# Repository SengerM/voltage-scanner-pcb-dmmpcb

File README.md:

# voltage-scanner-pcb-dmmpcb

[KiCad](http://kicad-pcb.org/) project for the DMMPCB board. This board implements the handling of the voltmeter. The schematic of this board can be found in [this link](export/DMMPCB.pdf). Below is the layout.

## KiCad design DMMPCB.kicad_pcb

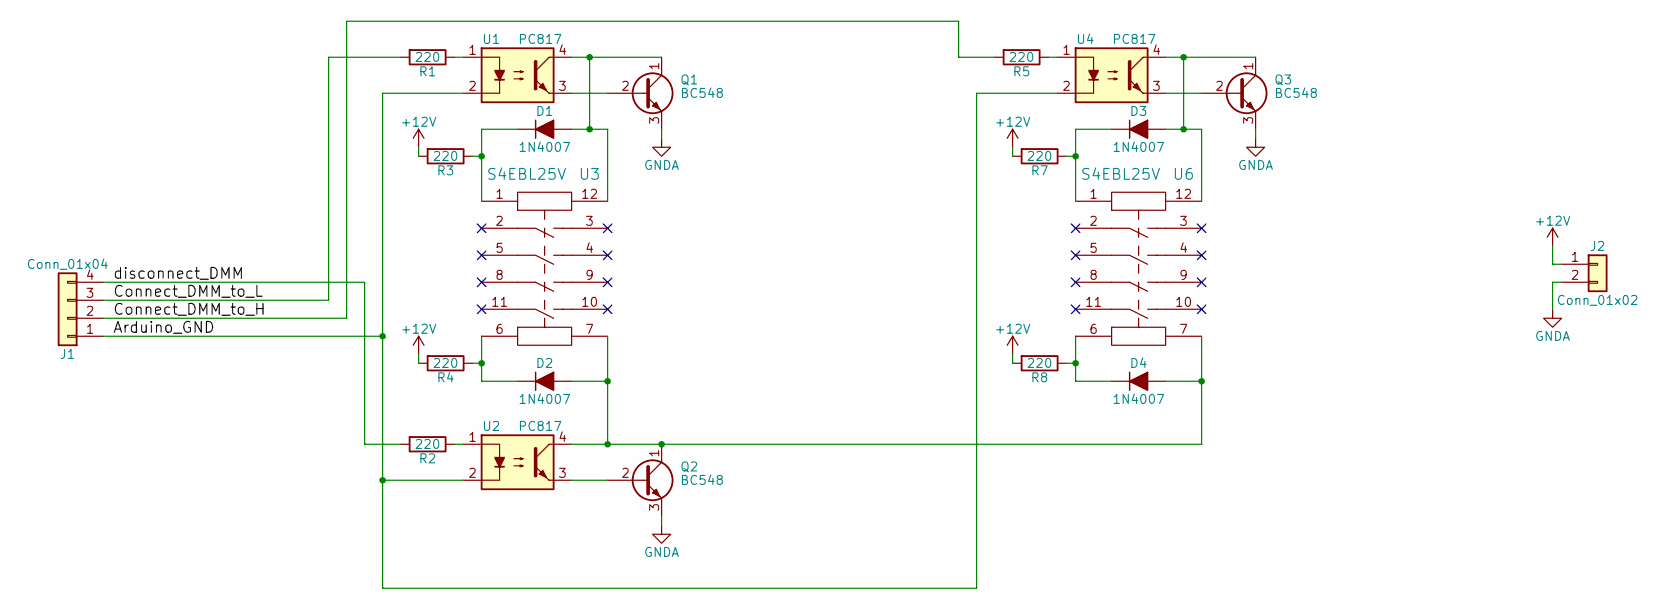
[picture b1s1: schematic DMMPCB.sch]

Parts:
D1, D2, D3, D4: 1N4007; D_SMA-SMB_Universal_Handsoldering
J1: Conn_01x04; Pin_Header_Straight_1x04_Pitch2.54mm
J2: Conn_01x02; Pin_Header_Straight_2x01_Pitch2.54mm
Q1, Q2, Q3: BC548; TO-92_Molded_Narrow_CUSTOM_PADS
R1, R2, R3, R4, R5, R7, R8: 220; R_1206_HandSoldering
U1, U2, U4: PC817; DIP-4_W7.62mm
U3, U6: S4EBL25V

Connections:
+12V: J2.1, R3.2, R4.2, R7.2, R8.2
/Arduino_GND: J1.1, U1.2, U2.2, U4.2
/Connect_DMM_to_H: J1.2, R5.2
/Connect_DMM_to_L: J1.3, R1.2
/disconnect_DMM: J1.4, R2.2
GNDA: J2.2, Q1.3 (E), Q2.3 (E), Q3.3 (E)
unnamed: D1.1 (K), R3.1, U3.1
unnamed: D1.2 (A), Q1.1 (C), U1.4, U3.12
unnamed: D2.1 (K), R4.1, U3.6
unnamed: D2.2 (A), D4.2 (A), Q2.1 (C), U2.4, U3.7, U6.7
unnamed: D3.1 (K), R7.1, U6.1
unnamed: D3.2 (A), Q3.1 (C), U4.4, U6.12
unnamed: D4.1 (K), R8.1, U6.6
unnamed: Q1.2 (B), U1.3
unnamed: Q2.2 (B), U2.3
unnamed: Q3.2 (B), U4.3
unnamed: R1.1, U1.1
unnamed: R2.1, U2.1
unnamed: R5.1, U4.1

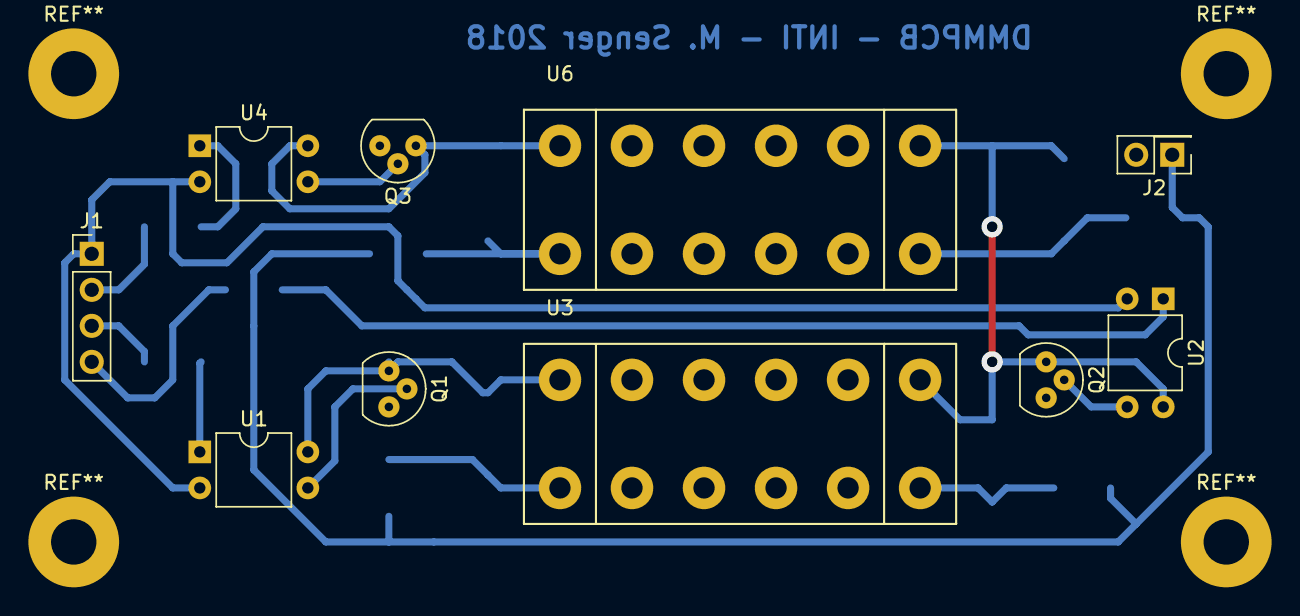
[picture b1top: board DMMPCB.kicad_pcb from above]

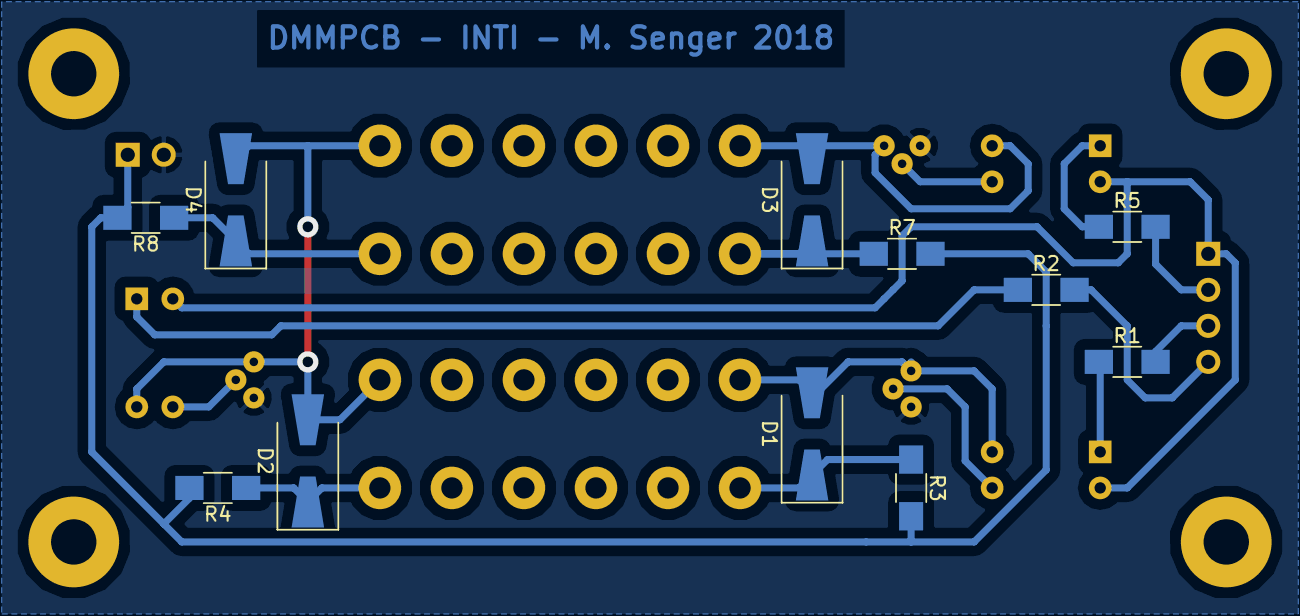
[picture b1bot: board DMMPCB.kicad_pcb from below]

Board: 2 copper layers, 21 parts (11 on the bottom side), 19 nets.

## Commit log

2019-05-23 Added readme
